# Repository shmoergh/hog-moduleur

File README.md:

# Hog Moduleur

Fully analog DIY-friendly modular synth. Project is under development.

Follow the progress on [shmoergh.com](https://www.shmoergh.com/hog-moduleur/) — consider [subscribing to the newsletter](https://www.shmoergh.com/hog-moduleur/#/portal/signup) to get the latest updates in your inbox.

## Modules

- [00 — Eurorack frame](https://github.com/shmoergh/hog-moduleur/tree/main/00-eurorack-frame)
- [01 — Power supply](https://github.com/shmoergh/hog-moduleur/tree/main/01-psu)

## License

Shmøergh Hog Moduleur © 2024

Hardware is licensed under [CC BY-NC 4.0](https://creativecommons.org/licenses/by-nc/4.0/)

Software is licensed under [MIT](https://opensource.org/license/mit).

Font used on PCBs: https://departuremono.com

Simulations made in [CircuitJS](https://www.falstad.com/circuit/circuitjs.html)

## Disclaimer

All electronic projects and designs presented on this web site, or associated web sites should be considered dangerous if not lethal if not used safely. When working on projects based on the designs on this site, use extreme care to ensure that you do not come into contact with mains AC voltages or high voltage DC. If you are not confident about working with mains voltages, or high voltages, or you are not legally allowed to work with mains voltages, or high voltages, you are advised not to attempt work on them. The author, host, and all people associated with these web pages disclaim any liability for damages should anyone be killed or injured while working on these projects, or projects based on these designs, or any other project or design presented on these web pages and any associated web pages. The author, host, and all people associated with these web pages also disclaim any liability for projects, or projects based on these designs, or any other project or design presented on these web pages and any associated web pages when used in such a way as to infringe relevant government regulations and by-laws.

All circuits, schematics, printed circuit board, panel design and associated data published on this site can be used for private use only.

We are not responsible for any errors in the PCB design or the parts list. All responsibility for ordering PCBs, components, and assembly services rests solely with you.

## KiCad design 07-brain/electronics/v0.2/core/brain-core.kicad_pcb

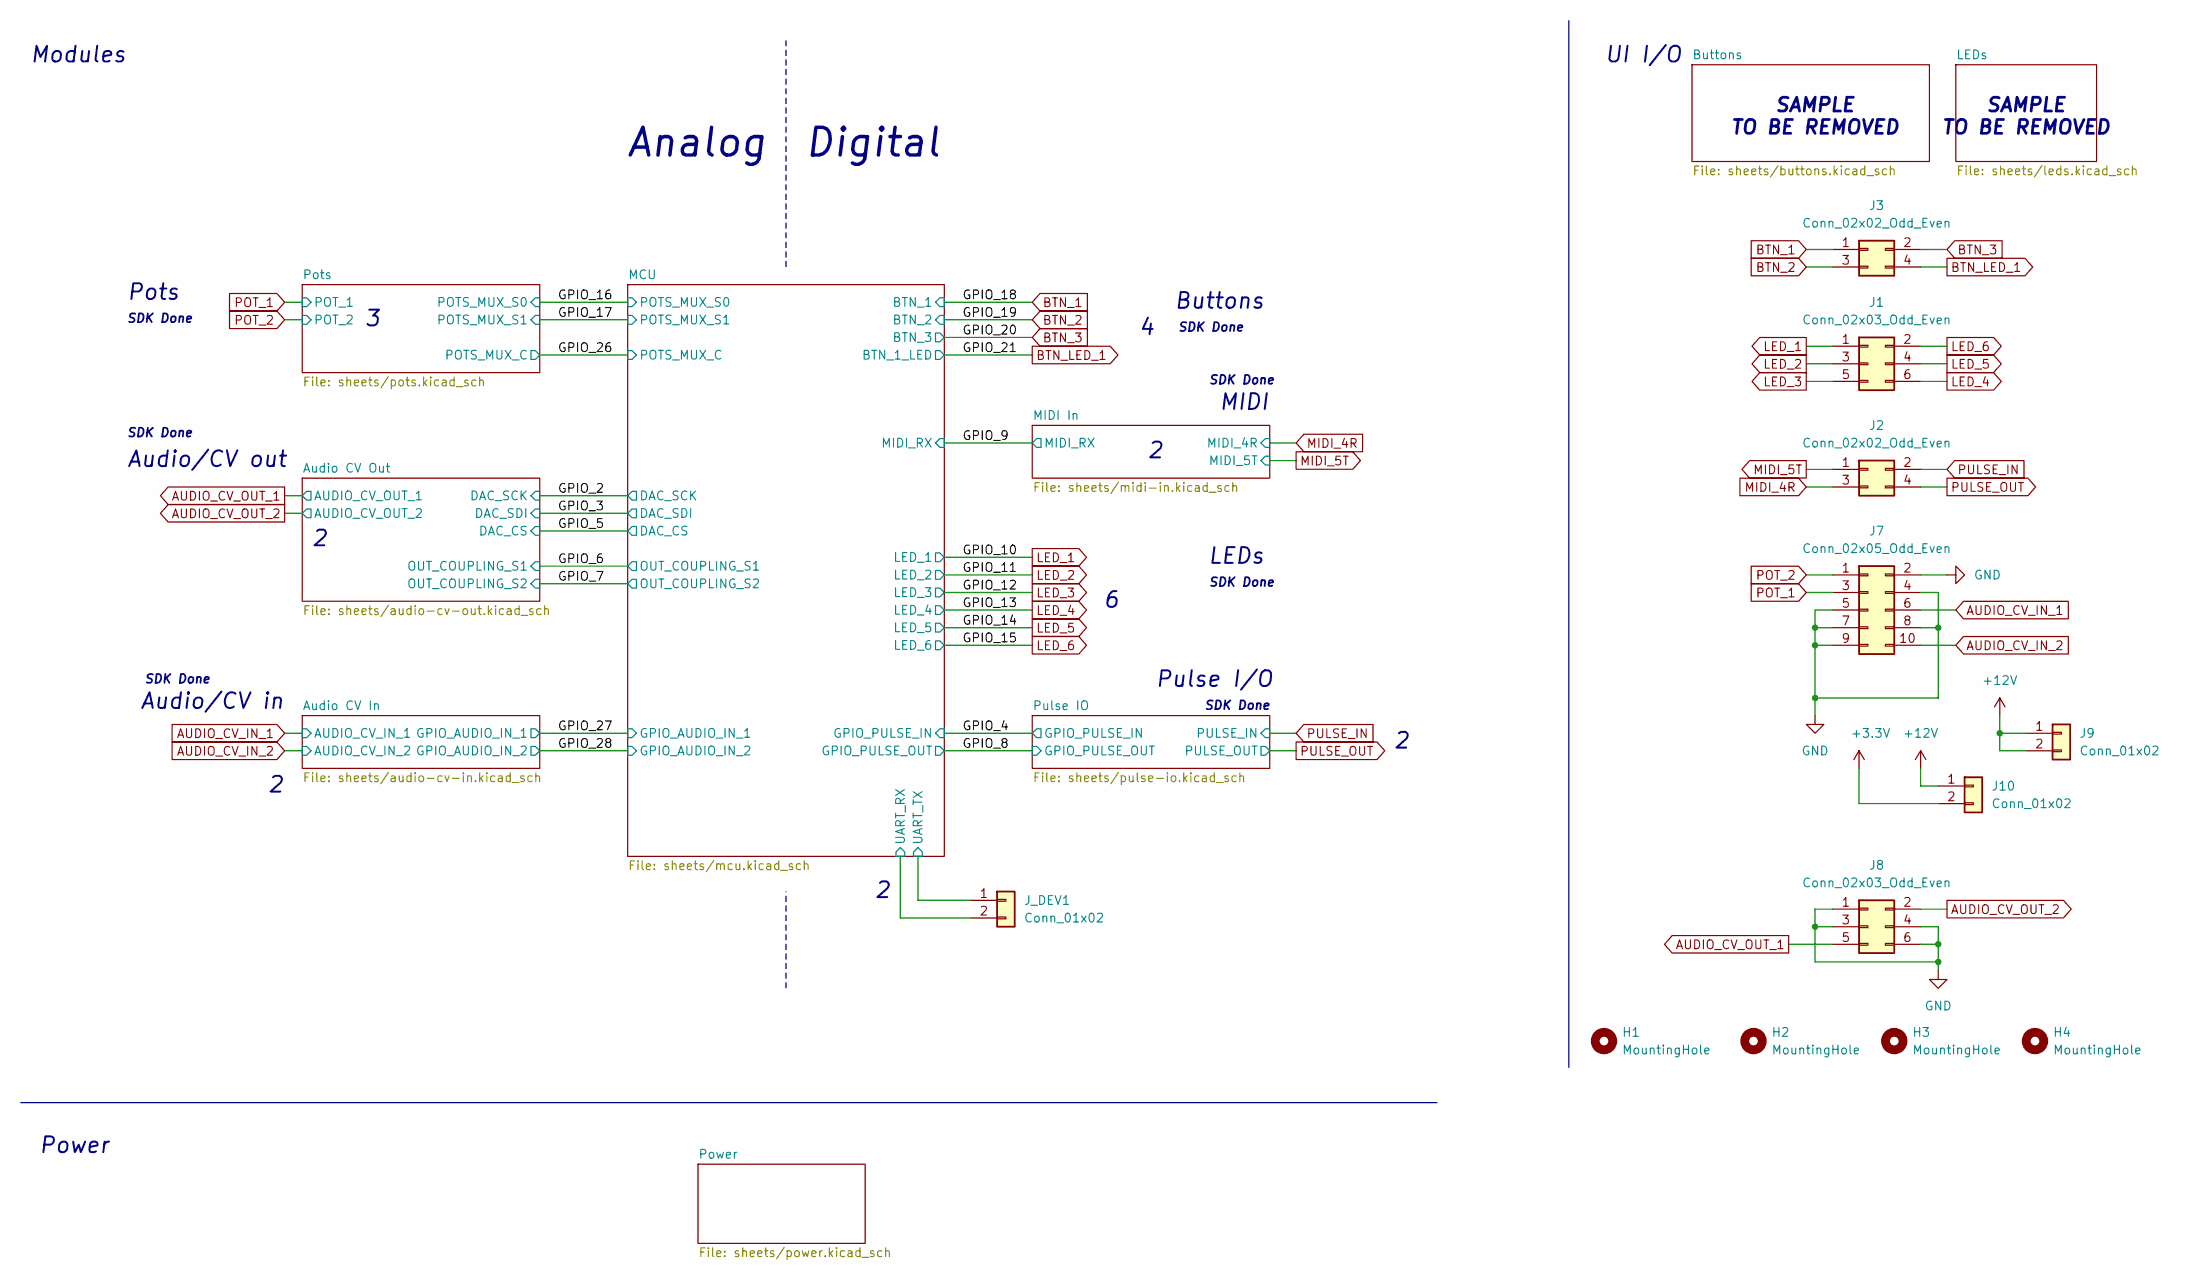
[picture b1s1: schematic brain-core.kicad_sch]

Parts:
H1, H2, H3, H4: MountingHole; MountingHole_3.2mm_M3_DIN965_Pad
J1, J8: Conn_02x03_Odd_Even; PinHeader_2x03_P2.54mm_Vertical
J2, J3: Conn_02x02_Odd_Even; PinHeader_2x02_P2.54mm_Vertical
J7: Conn_02x05_Odd_Even; PinHeader_2x05_P2.54mm_Vertical
J9, J10: Conn_01x02; PinHeader_1x02_P2.54mm_Vertical
J_DEV1: Conn_01x02; PinHeader_1x02_P2.54mm_Vertical

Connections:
+12V: J9.1, J9.2, J10.1; also elsewhere on the board
/MCU/UART_RX: J_DEV1.2; also elsewhere on the board
/MCU/UART_TX: J_DEV1.1; also elsewhere on the board
AUDIO_CV_IN_1: J7.6; also elsewhere on the board
AUDIO_CV_IN_2: J7.10; also elsewhere on the board
AUDIO_CV_OUT_1: J8.5; also elsewhere on the board
AUDIO_CV_OUT_2: J8.2; also elsewhere on the board
BTN_1: J3.1; also elsewhere on the board
BTN_2: J3.3; also elsewhere on the board
BTN_3: J3.2; also elsewhere on the board
BTN_LED_1: J3.4; also elsewhere on the board
LED_1: J1.1; also elsewhere on the board
LED_2: J1.3; also elsewhere on the board
LED_3: J1.5; also elsewhere on the board
LED_4: J1.6; also elsewhere on the board
LED_5: J1.4; also elsewhere on the board
LED_6: J1.2; also elsewhere on the board
POT_1: J7.3; also elsewhere on the board
POT_2: J7.1; also elsewhere on the board
PULSE_IN: J2.2; also elsewhere on the board
PULSE_OUT: J2.4; also elsewhere on the board

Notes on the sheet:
Power
Audio/CV in
SAMPLE TO BE REMOVED
Pulse I/O
Audio/CV out
SDK Done
LEDs
Modules
Buttons
Analog
Pots
Digital
MIDI
UI I/O

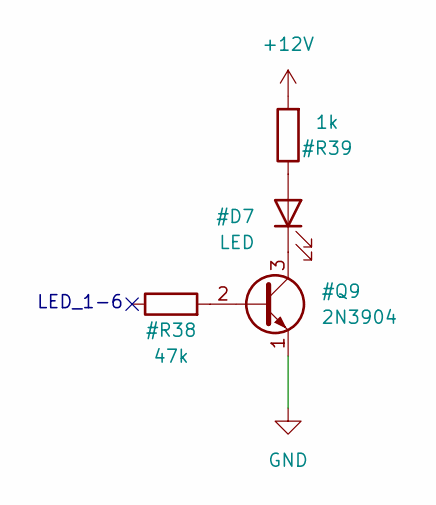
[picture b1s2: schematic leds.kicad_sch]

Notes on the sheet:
LED_1-6

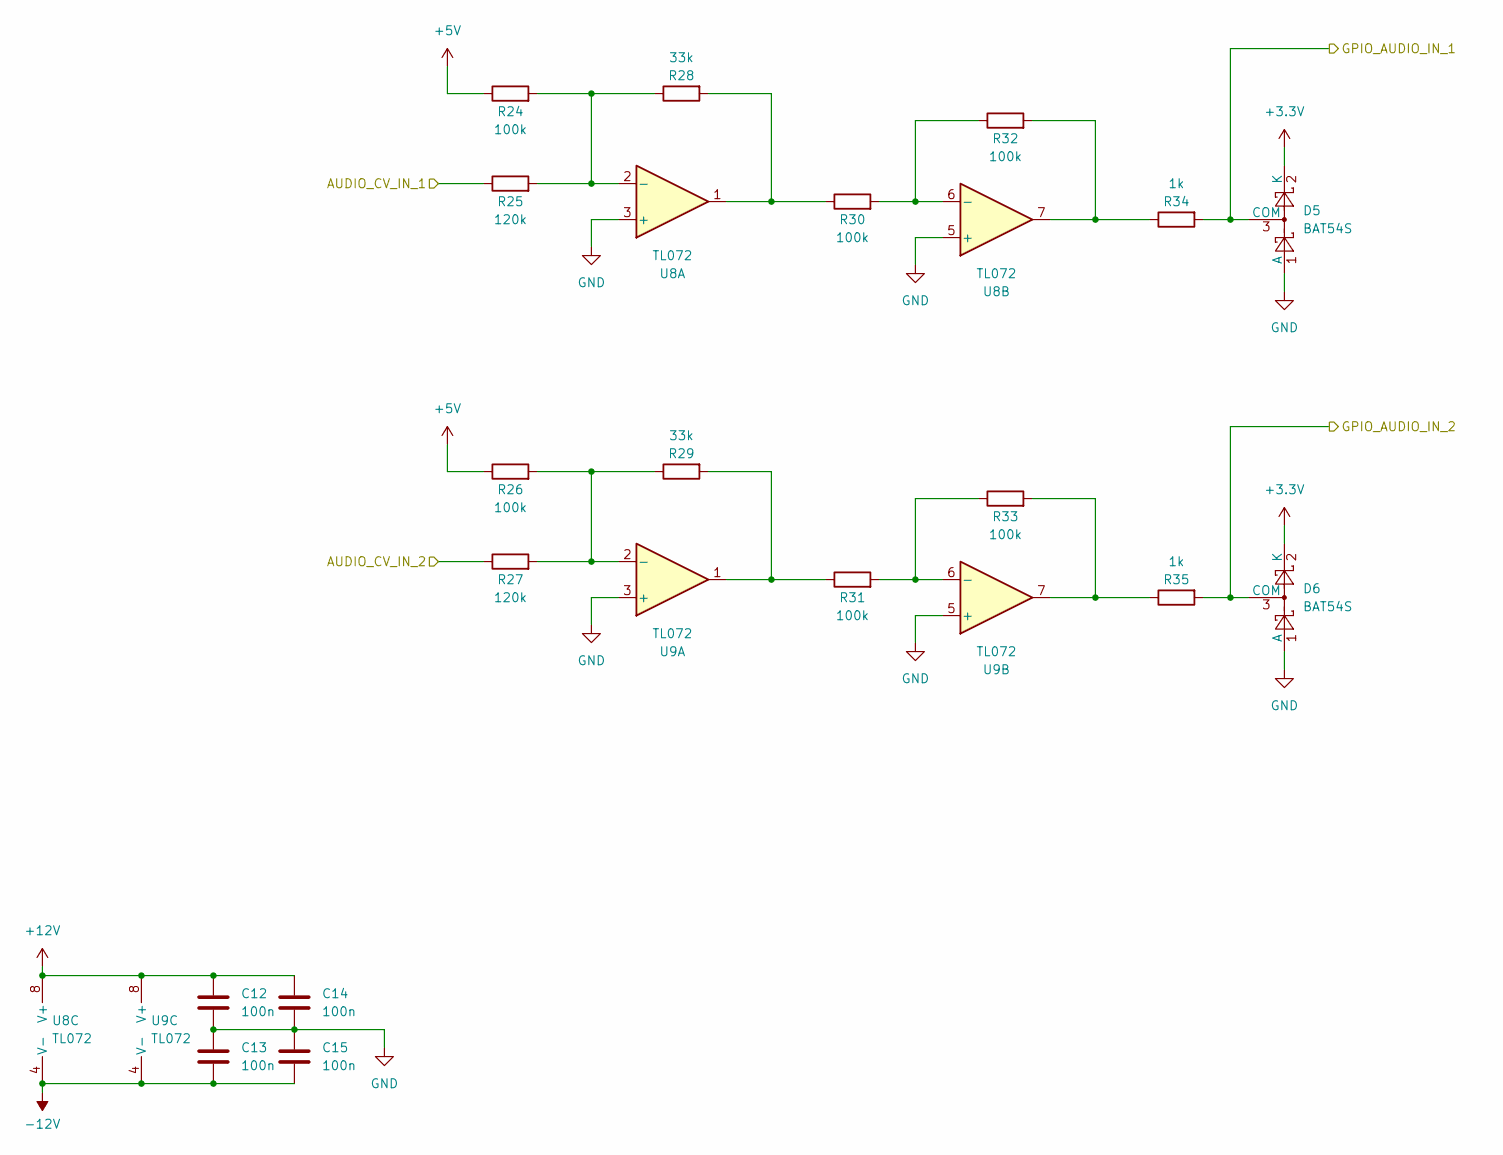
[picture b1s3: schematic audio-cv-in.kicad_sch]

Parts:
C12, C13, C14, C15: 100n; C_0603_1608Metric; LCSC C14663
D5, D6: BAT54S; SOT-23; LCSC C7420333
R24, R26, R30, R31, R32, R33: 100k; R_0603_1608Metric; LCSC C25803
R25, R27: 120k; R_0603_1608Metric; LCSC C25808
R28, R29: 33k; R_0603_1608Metric; LCSC C4216
R34, R35: 1k; R_0603_1608Metric; LCSC C21190
U8, U9: TL072; SOIC-8_3.9x4.9mm_P1.27mm; LCSC C6961

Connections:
+5V: R24.1, R26.1; also elsewhere on the board
+12V: C12.1, C14.1, U8.8 (V+), U9.8 (V+); also elsewhere on the board
-12V: C13.2, C15.2, U8.4 (V-), U9.4 (V-); also elsewhere on the board
/GPIO_27: D5.3 (COM), R34.2; also elsewhere on the board
/GPIO_28: D6.3 (COM), R35.2; also elsewhere on the board
AUDIO_CV_IN_1: R25.1; also elsewhere on the board
AUDIO_CV_IN_2: R27.1; also elsewhere on the board
unnamed: R28.2, R30.1, U8.1
unnamed: R29.2, R31.1, U9.1
unnamed: R32.2, R34.1, U8.7
unnamed: R33.2, R35.1, U9.7
unnamed: R24.2, R25.2, R28.1, U8.2 (-)
unnamed: R30.2, R32.1, U8.6 (-)
unnamed: R26.2, R27.2, R29.1, U9.2 (-)
unnamed: R31.2, R33.1, U9.6 (-)

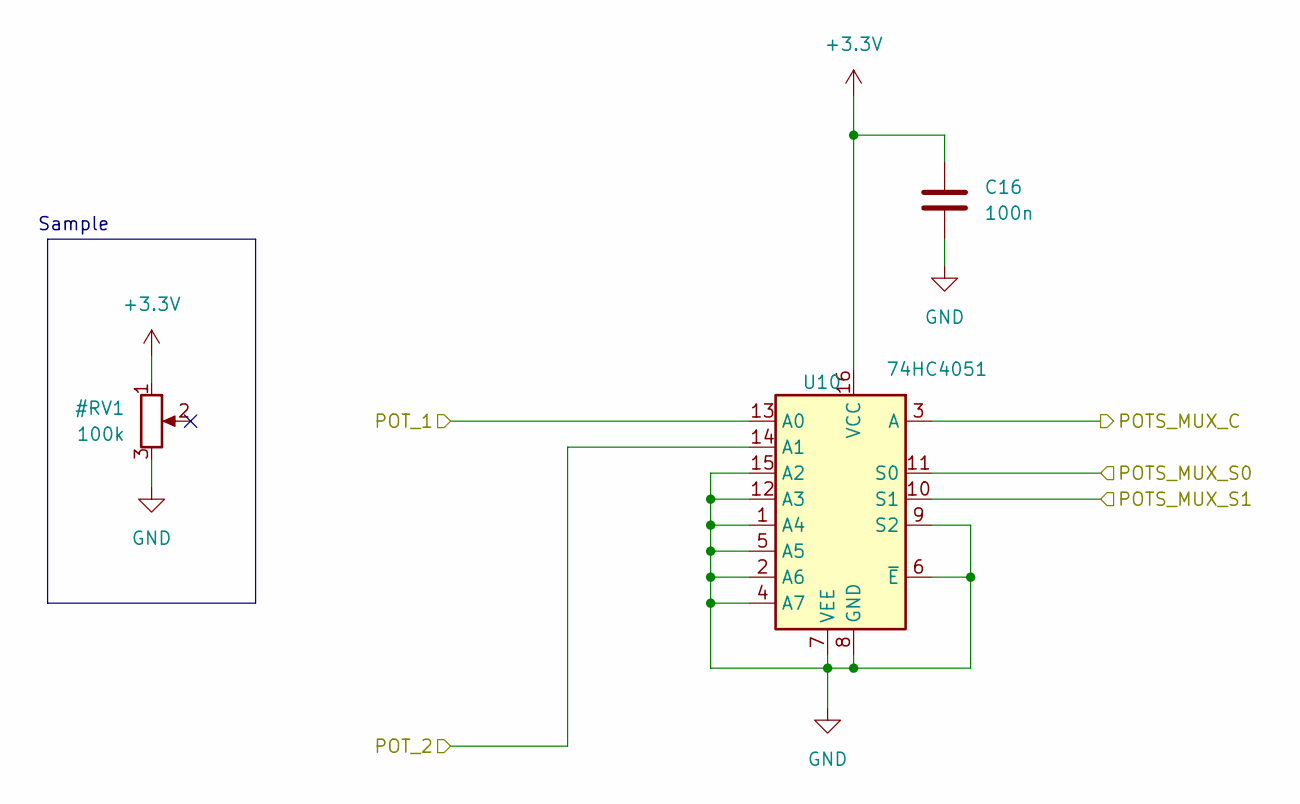
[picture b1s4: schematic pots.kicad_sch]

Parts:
C16: 100n; C_0603_1608Metric; LCSC C14663
U10: 74HC4051; SOIC-16_3.9x9.9mm_P1.27mm; LCSC C9386

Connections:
/GPIO_16: U10.11 (S0); also elsewhere on the board
/GPIO_17: U10.10 (S1); also elsewhere on the board
/GPIO_26: U10.3 (A); also elsewhere on the board
POT_1: U10.13 (A0); also elsewhere on the board
POT_2: U10.14 (A1); also elsewhere on the board

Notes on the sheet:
Sample

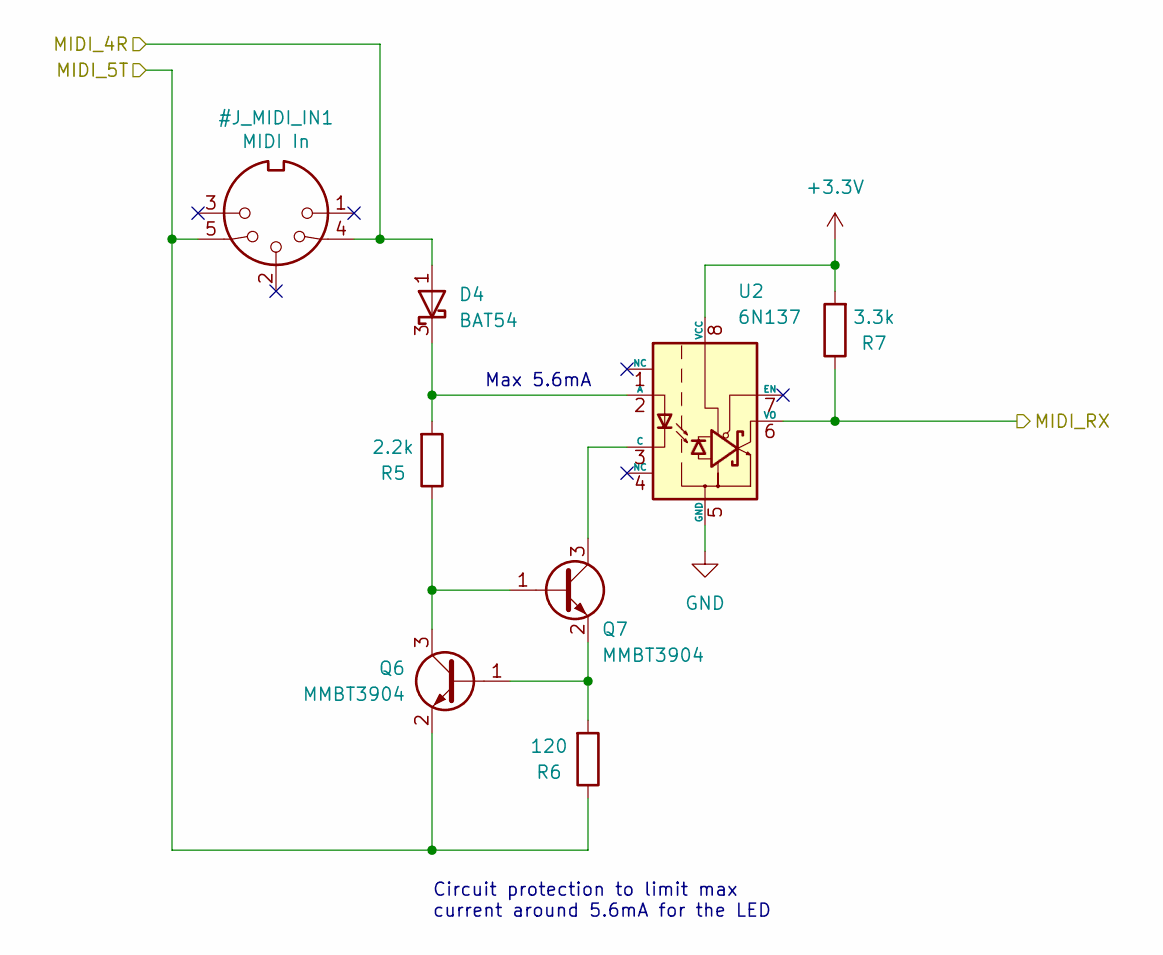
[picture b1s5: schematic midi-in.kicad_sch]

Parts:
D4: BAT54; SOT-23; LCSC C22466368
Q6, Q7: MMBT3904; SOT-23; LCSC C20526
R5: 2.2k; R_0603_1608Metric; LCSC C4190
R6: 120; R_0603_1608Metric; LCSC C22787
R7: 3.3k; R_0603_1608Metric; LCSC C22978
U2: 6N137; SOP-8_6.605x9.655mm_P2.54mm; LCSC C92651

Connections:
/GPIO_9: R7.1, U2.6 (VO); also elsewhere on the board
unnamed: D4.3 (K), R5.2, U2.2 (A)
unnamed: Q6.1 (B), Q7.2 (E), R6.2
unnamed: Q6.3 (C), Q7.1 (B), R5.1
unnamed: Q7.3 (C), U2.3 (C)

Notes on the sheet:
Max 5.6mA
Circuit protection to limit max current around 5.6mA for the LED

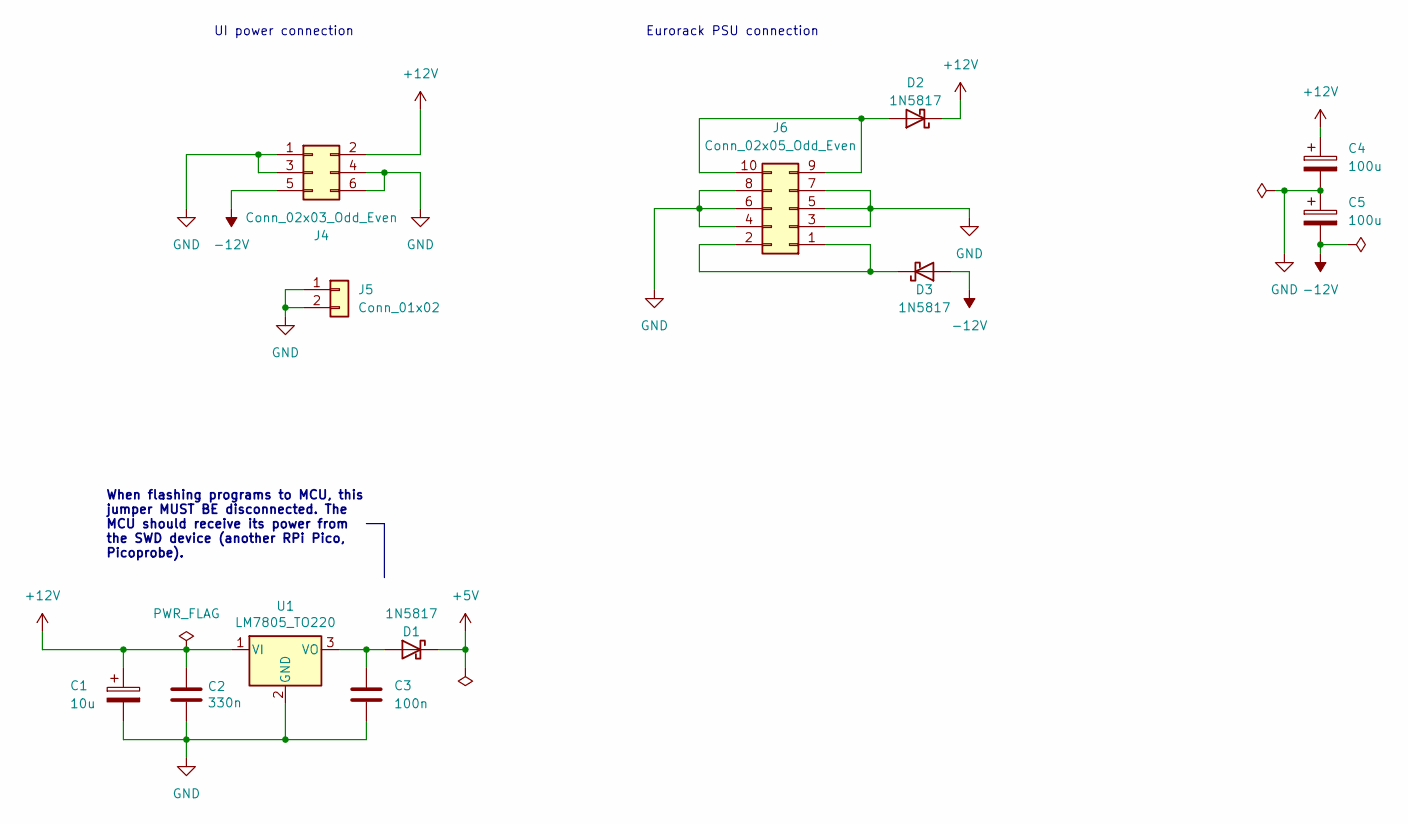
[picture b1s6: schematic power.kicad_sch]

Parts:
C1: 10u; CP_Elec_4x5.4; LCSC C46550410
C2: 330n; C_0603_1608Metric_Pad1.08x0.95mm_HandSolder; LCSC C188679
C3: 100n; C_0603_1608Metric; LCSC C14663
C4, C5: 100u; CP_Elec_6.3x7.7; LCSC C2836437
D1, D2, D3: 1N5817; D_SOD-323; LCSC C5190152
J4: Conn_02x03_Odd_Even; PinHeader_2x03_P2.54mm_Vertical
J5: Conn_01x02; PinHeader_1x02_P2.54mm_Vertical
J6: Conn_02x05_Odd_Even; IDC-Header_2x05_P2.54mm_Horizontal
U1: LM7805_TO220; TO-220-3_Horizontal_TabDown; Part No. 926-LM7805CT/NOPB

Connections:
+5V: D1.1 (K); also elsewhere on the board
+12V: C1.1, C2.1, C4.1, D2.1 (K), J4.2, U1.1 (VI); also elsewhere on the board
-12V: C5.2, D3.2 (A), J4.5; also elsewhere on the board
unnamed: C3.1, D1.2 (A), U1.3 (VO)
unnamed: D2.2 (A), J6.9, J6.10
unnamed: D3.1 (K), J6.1, J6.2

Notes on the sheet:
UI power connection
When flashing programs to MCU, this jumper MUST BE disconnected. The MCU should receive its power from the SWD device (another RPi Pico, Picoprobe).
Eurorack PSU connection

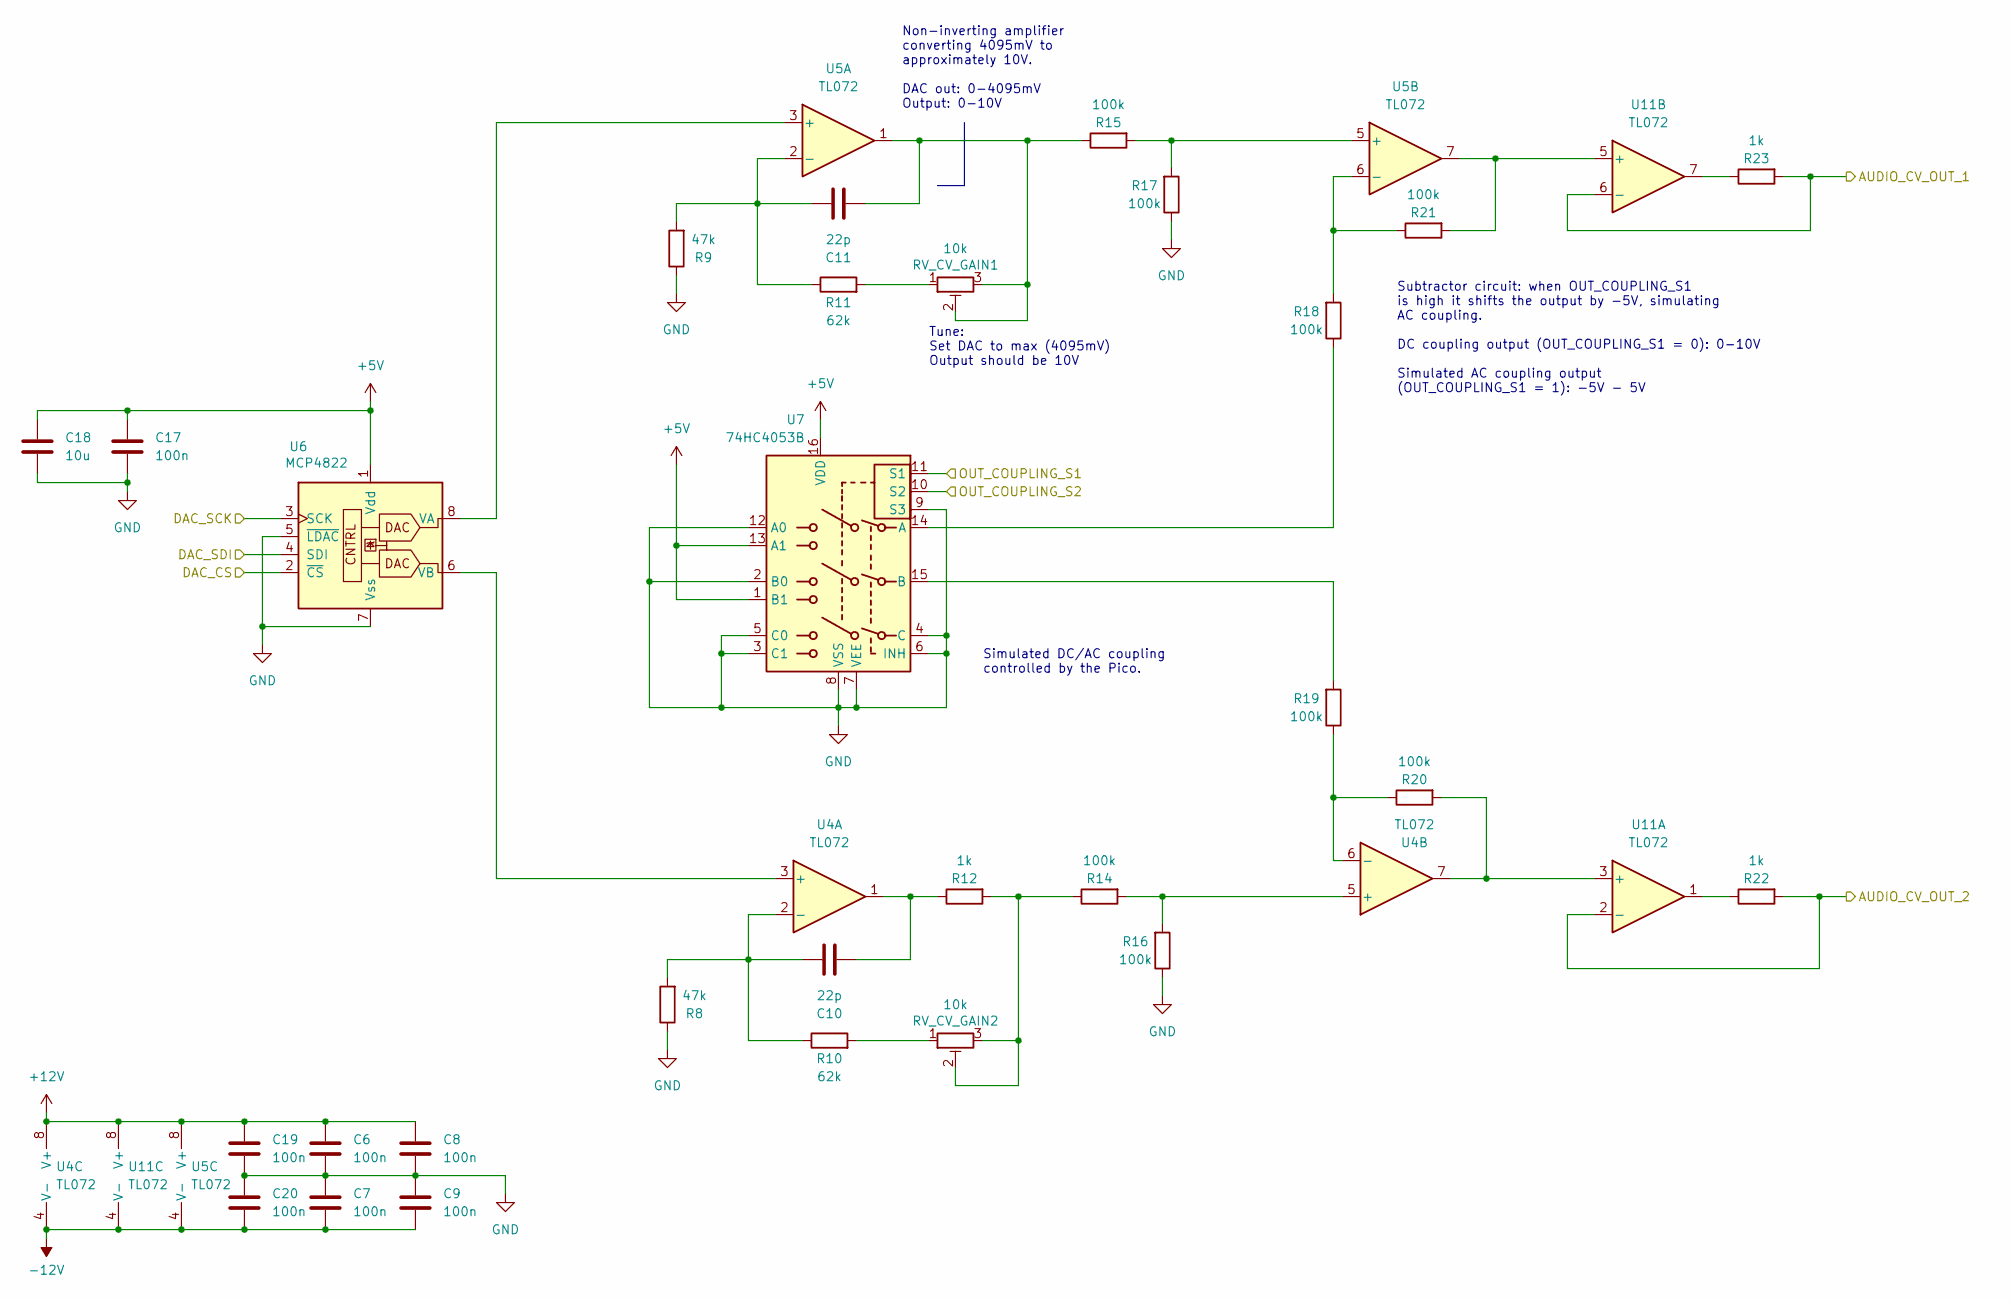
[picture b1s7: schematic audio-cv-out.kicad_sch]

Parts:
C6, C7, C8, C9, C17, C19, C20: 100n; C_0603_1608Metric; LCSC C14663
C10, C11: 22p; C_0603_1608Metric; LCSC C1653
C18: 10u; C_0603_1608Metric; LCSC C19702
R8, R9: 47k; R_0603_1608Metric; LCSC C25819
R10, R11: 62k; R_0603_1608Metric; LCSC C23221
R12, R22, R23: 1k; R_0603_1608Metric; LCSC C21190
R14, R15, R16, R17, R18, R19, R20, R21: 100k; R_0603_1608Metric; LCSC C25803
RV_CV_GAIN1, RV_CV_GAIN2: 10k; Potentiometer_ACP_CA6-H2,5_Horizontal; Part No. 531-PT6KH-10K
U4, U5, U11: TL072; SOIC-8_3.9x4.9mm_P1.27mm; LCSC C6961
U6: MCP4822; SOIC-8_3.9x4.9mm_P1.27mm; LCSC C623653
U7: 74HC4053B; SOIC-16_3.9x9.9mm_P1.27mm; LCSC C5647

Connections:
+5V: C17.1, C18.1, U6.1 (Vdd), U7.1 (B1), U7.13 (A1), U7.16 (VDD); also elsewhere on the board
+12V: C6.1, C8.1, C19.1, U4.8 (V+), U5.8 (V+), U11.8 (V+); also elsewhere on the board
-12V: C7.2, C9.2, C20.2, U4.4 (V-), U5.4 (V-), U11.4 (V-); also elsewhere on the board
/GPIO_2: U6.3 (SCK); also elsewhere on the board
/GPIO_3: U6.4 (SDI); also elsewhere on the board
/GPIO_5: U6.2 (~CS); also elsewhere on the board
/GPIO_6: U7.11 (S1); also elsewhere on the board
/GPIO_7: U7.10 (S2); also elsewhere on the board
AUDIO_CV_OUT_1: R23.2, U11.6 (-); also elsewhere on the board
AUDIO_CV_OUT_2: R22.2, U11.2 (-); also elsewhere on the board
unnamed: C10.2, R12.1, U4.1
unnamed: C11.2, R15.1, RV_CV_GAIN1.2, RV_CV_GAIN1.3, U5.1
unnamed: R10.2, RV_CV_GAIN2.1
unnamed: R11.2, RV_CV_GAIN1.1
unnamed: R12.2, R14.1, RV_CV_GAIN2.2, RV_CV_GAIN2.3
unnamed: R22.1, U11.1
unnamed: R23.1, U11.7
unnamed: U4.3 (+), U6.6 (VB)
unnamed: C10.1, R8.2, R10.1, U4.2 (-)
unnamed: R14.2, R16.2, U4.5 (+)
unnamed: R19.1, R20.1, U4.6 (-)
unnamed: U5.3 (+), U6.8 (VA)
unnamed: C11.1, R9.2, R11.1, U5.2 (-)
unnamed: R15.2, R17.2, U5.5 (+)
unnamed: R18.2, R21.1, U5.6 (-)
unnamed: R18.1, U7.14 (A)
unnamed: R19.2, U7.15 (B)
unnamed: R20.2, U4.7, U11.3 (+)
unnamed: R21.2, U5.7, U11.5 (+)

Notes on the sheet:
Simulated DC/AC coupling controlled by the Pico.
Subtractor circuit: when OUT_COUPLING_S1 is high it shifts the output by -5V, simulating AC coupling. DC coupling output (OUT_COUPLING_S1 = 0): 0-10V Simulated AC coupling output (OUT_COUPLING_S1 = 1): -5V - 5V
Tune: Set DAC to max (4095mV) Output should be 10V
Non-inverting amplifier converting 4095mV to approximately 10V. DAC out: 0-4095mV Output: 0-10V

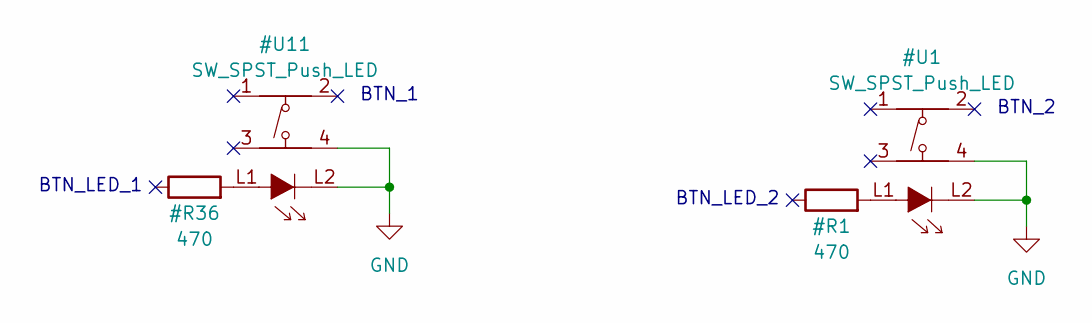
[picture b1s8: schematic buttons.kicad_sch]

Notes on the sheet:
BTN_LED_1
BTN_LED_2
BTN_2
BTN_1

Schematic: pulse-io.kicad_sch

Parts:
Q1, Q3: MMBT3904; SOT-23; LCSC C20526
R1: 100k; R_0603_1608Metric; LCSC C25803
R2: 3.3k; R_0603_1608Metric; LCSC C22978
R3: 10k; R_0603_1608Metric; LCSC C25804
R4: 7.5k; R_0603_1608Metric; LCSC C23234

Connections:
+12V: R3.2; also elsewhere on the board
/GPIO_4: Q1.3 (C); also elsewhere on the board
/GPIO_8: R2.1; also elsewhere on the board
unnamed: Q1.1 (B), R1.2
unnamed: Q3.1 (B), R2.2
PULSE_IN: R1.1; also elsewhere on the board
PULSE_OUT: Q3.3 (C), R3.1, R4.2; also elsewhere on the board

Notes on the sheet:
About 5.1V pulses
Use Pico's pull up resistor to set value to logical 1. On pulse in, it goes to 0.
Pulse is inverted. Since the input is inverted too, if you just want to let pulses through you don't need to invert anything.

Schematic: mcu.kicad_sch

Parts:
J11: Conn_01x01; PinHeader_1x01_P2.54mm_Vertical
J13: Conn_01x03; PinHeader_1x03_P2.54mm_Vertical
J_USB_C_EXTENSION1: USB_C_Receptacle_USB2.0_16P; USB_C_Receptacle_HRO_TYPE-C-31-M-12; LCSC C165948
R36, R37: 5.1k; R_0603_1608Metric; LCSC C23186
SW1: SW_SPST; SW_Tactile_SKHH_Angled
U3: Pico; RaspberryPi_Pico_Common_Unspecified

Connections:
+5V: U3.39 (VSYS); also elsewhere on the board
/GPIO_2: U3.4 (GPIO2); also elsewhere on the board
/GPIO_3: U3.5 (GPIO3); also elsewhere on the board
/GPIO_4: U3.6 (GPIO4); also elsewhere on the board
/GPIO_5: U3.7 (GPIO5); also elsewhere on the board
/GPIO_6: U3.9 (GPIO6); also elsewhere on the board
/GPIO_7: U3.10 (GPIO7); also elsewhere on the board
/GPIO_8: U3.11 (GPIO8); also elsewhere on the board
/GPIO_9: U3.12 (GPIO9); also elsewhere on the board
/GPIO_16: U3.22 (GPIO17); also elsewhere on the board
/GPIO_17: U3.21 (GPIO16); also elsewhere on the board
/GPIO_26: U3.31 (GPIO26_ADC0); also elsewhere on the board
/GPIO_27: U3.32 (GPIO27_ADC1); also elsewhere on the board
/GPIO_28: U3.34 (GPIO28_ADC2); also elsewhere on the board
/MCU/TP1: J13.3, J_USB_C_EXTENSION1.A1 (GND), J_USB_C_EXTENSION1.A12 (GND), J_USB_C_EXTENSION1.B1 (GND), J_USB_C_EXTENSION1.B12 (GND), U3.44 (TP1)
/MCU/TP2: J13.1, J_USB_C_EXTENSION1.A7 (D-), J_USB_C_EXTENSION1.B7 (D-), U3.45 (TP2)
/MCU/TP3: J13.2, J_USB_C_EXTENSION1.A6 (D+), J_USB_C_EXTENSION1.B6 (D+), U3.46 (TP3)
/MCU/TP6: J11.1, SW1.1 (A), U3.47 (TP6)
/MCU/UART_RX: U3.2 (GPIO1); also elsewhere on the board
/MCU/UART_TX: U3.1 (GPIO0); also elsewhere on the board
BTN_1: U3.24 (GPIO18); also elsewhere on the board
BTN_2: U3.25 (GPIO19); also elsewhere on the board
BTN_3: U3.26 (GPIO20); also elsewhere on the board
BTN_LED_1: U3.27 (GPIO21); also elsewhere on the board
LED_1: U3.14 (GPIO10); also elsewhere on the board
LED_2: U3.15 (GPIO11); also elsewhere on the board
LED_3: U3.16 (GPIO12); also elsewhere on the board
LED_4: U3.17 (GPIO13); also elsewhere on the board
LED_5: U3.19 (GPIO14); also elsewhere on the board
LED_6: U3.20 (GPIO15); also elsewhere on the board
unnamed: J_USB_C_EXTENSION1.A5 (CC1), R36.1
unnamed: J_USB_C_EXTENSION1.B5 (CC2), R37.1
unnamed: J_USB_C_EXTENSION1.A4 (VBUS), J_USB_C_EXTENSION1.A9 (VBUS), J_USB_C_EXTENSION1.B4 (VBUS), J_USB_C_EXTENSION1.B9 (VBUS), U3.40 (VBUS)

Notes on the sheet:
TP2 — USB- (USB Minus) TP3 — USB+ (USB Plus) TP1 - GND
Solder these to TP's on the Raspberry Pi Pico:

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
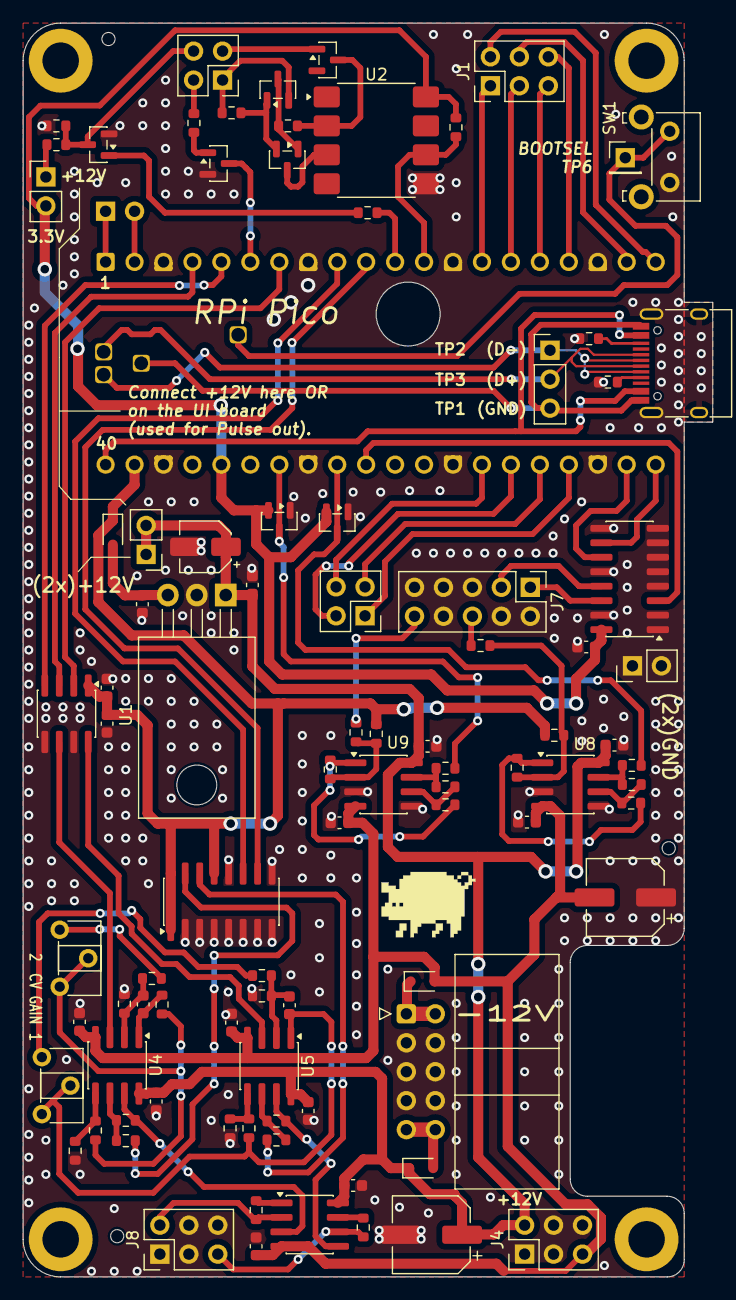
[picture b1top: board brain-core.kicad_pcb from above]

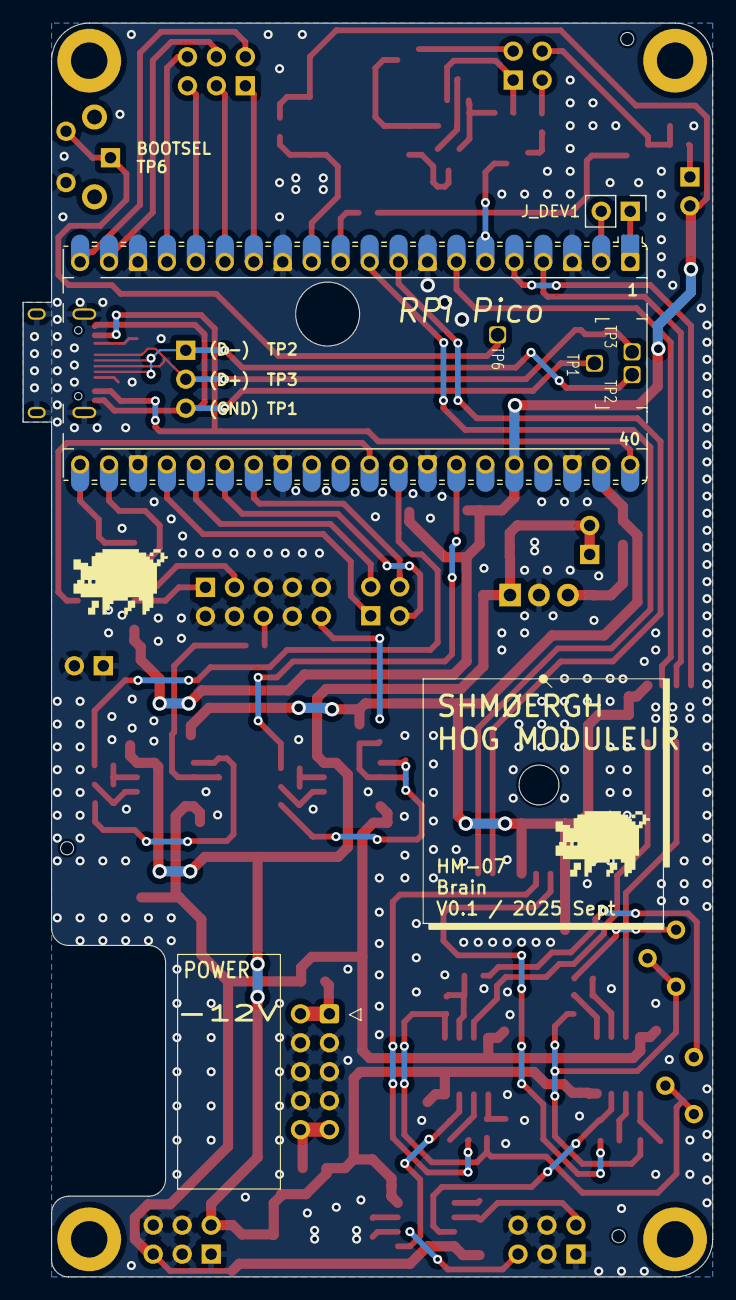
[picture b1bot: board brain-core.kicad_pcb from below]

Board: 2 copper layers, 60.5 x 110.0 mm, 98 parts (2 on the bottom side), 83 nets.
